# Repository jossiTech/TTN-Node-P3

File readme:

#DRAFT TTN Universal Node

(#LoRaWAN #The Things Network # TTN Universal Node  #ATmega 328p #RFM95W #1 Wire Busses #I2C #DHT11)

### Evaluation Board with nice Enclosure, providing plenty diffrent ports

# Introduction

I wanted a universal Node for The Things Network that provides diffrent ports for diffrent Purposes.
Becouse I don´t really like Breadboards I decided to design a little PCB that fits in a suitable enclosure. You can find the EAGLE-Files [here.](https://github.com/jossiTech/TTN-Node-P2/tree/master/Eagle-Files) 

* 1-Wire-Bus
* I2C
* Relais Port
* DHT11 / DHT22 Socket for temperature and humidity
* USB-B-Port for Input voltage
* Socket to connect an FTDI-Module for uploading new sketches
* SMA-Connector for Antenna

The node consist of an Arduino Pro Micro (3.3V) and a RFM95W Radio to communicate with „The Things Network.“ The RFM95W-Radio-Model use 3.3 Volt, so when using the 3.3 Volt Version of the Arduino Pro Micro no level shifting is necessary.
 
You find the suitable enclosure for the PCB by searching for "strabubox 524"
I have ordered a few PCBs from [Eurocircuits](https://www.eurocircuits.com/) and a few sets of components of my favorite chinese distributer. If you´re interested in the PCB or the PCB with the components and the enclosure you can find it on [Tindie.](https://www.tindie.com/stores/jossitech/)

[Here](https://github.com/jossiTech/TTN-Node-P2/tree/master/code) you can find the sketch that work fine for the board, feel free to use and modify it for your needs.

I descirbed HERE (add LINK) a straightforward way to visualize 4 temperatures and the humidity on Cayenne.

- The 328P comes with a Arduino Bootloader xyz
- Choose Arduino Nano 328P in the IDE when uploading new sketches

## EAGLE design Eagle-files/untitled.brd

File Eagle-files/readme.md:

### Eagle-files for The JossiTec P3 (1.1) PCB

A suitable case is available in which the PCB fits perfectly. Search for "strapubox 524"

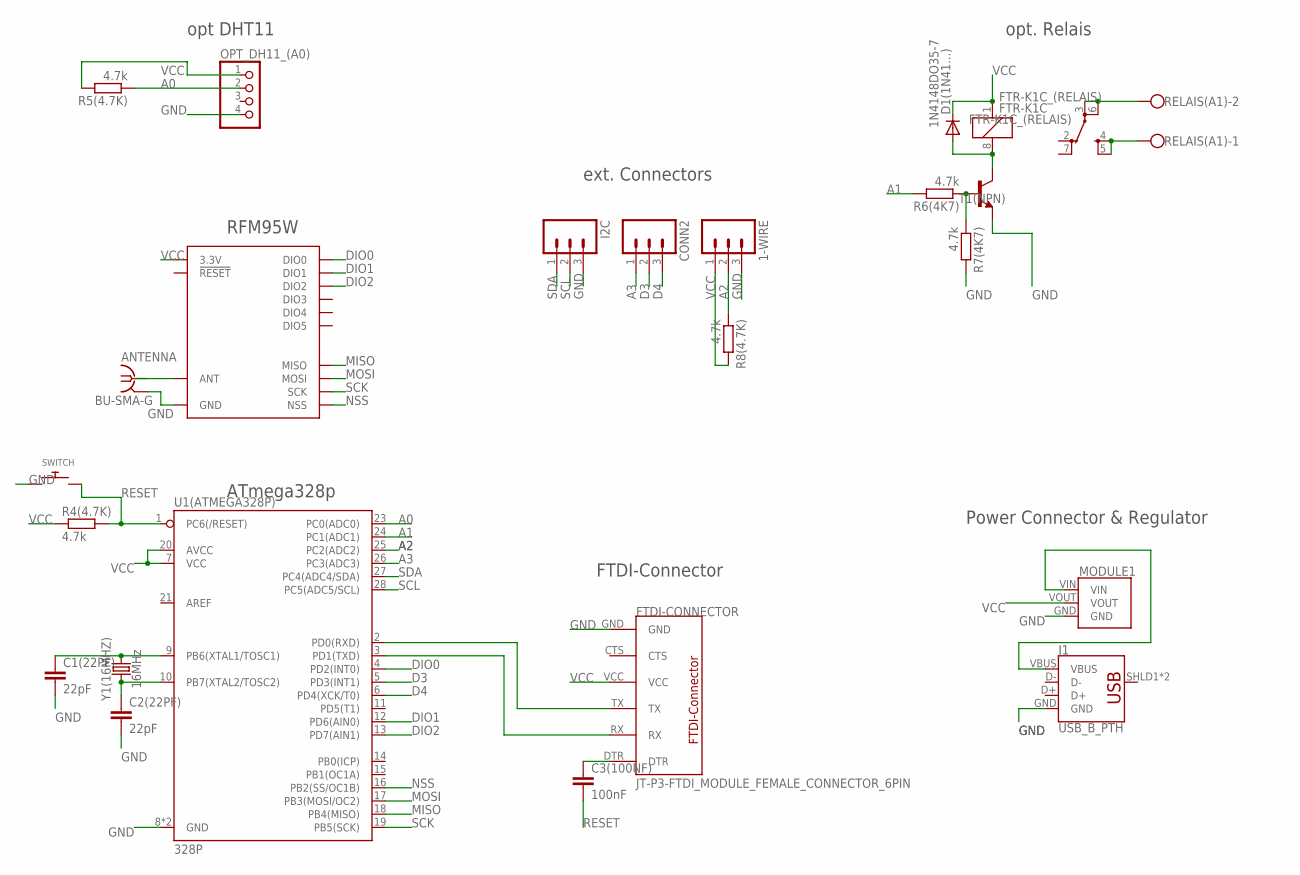
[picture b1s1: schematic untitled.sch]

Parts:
1-WIRE: M03; 03P
ANTENNA: BU-SMA-G
C1(22PF), C2(22PF): 22pF; CAP-PTH-2.54
C3(100NF): 100nF; CAP-PTH-2.54
CONN2: M03; 03P
D1(1N41...): 1N4148DO35-7; DO35-7
FTDI-CONNECTOR: JT-P3-FTDI_MODULE_FEMALE_CONNECTOR_6PIN
FTR-K1C_(RELAIS): FTR-K1C
I2C: M03; 03P
J1: USB_B_PTH; USB-B-PTH
MODULE1: JT-P3-VOLTAGEREGULATOR
OPT_DH11_(A0): PINHD-1X4; 1X04
R4(4.7K), R5(4.7K), R6(4K7), R7(4K7), R8(4.7K): 4.7k; 0207/10
RELAIS(A1): W237-102
SWITCH: SWITCH_PUSHBUTTONEVQ-PE; TACT_PANA-EVQ
T1(NPN): BC237-NPN-TO92-CBE; TO92-CBE
U1(ATMEGA328P): 328P; DIP28
U2: RFM95W; RFM95/96/97/98W
Y1(16MHZ): 16MHz; HC49US

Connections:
A0: OPT_DH11_(A0).2, R5(4.7K).1, U1(ATMEGA328P).23 (PC0(ADC0))
A1: R6(4K7).2, U1(ATMEGA328P).24 (PC1(ADC1))
A2: 1-WIRE.2, R8(4.7K).1, U1(ATMEGA328P).25 (PC2(ADC2))
A3: CONN2.1, U1(ATMEGA328P).26 (PC3(ADC3))
D3: CONN2.2, U1(ATMEGA328P).5 (PD3(INT1))
D4: CONN2.3, U1(ATMEGA328P).6 (PD4(XCK/T0))
DIO0: U1(ATMEGA328P).4 (PD2(INT0)), U2.DIO0
DIO1: U1(ATMEGA328P).12 (PD6(AIN0)), U2.DIO1
DIO2: U1(ATMEGA328P).13 (PD7(AIN1)), U2.DIO2
GND: 1-WIRE.3, ANTENNA.2, ANTENNA.3 (2), ANTENNA.4 (2), ANTENNA.5 (2), C1(22PF).2, C2(22PF).2, FTDI-CONNECTOR.GND, I2C.3, J1.GND, MODULE1.GND, OPT_DH11_(A0).4, R7(4K7).2, SWITCH.P$1, T1(NPN).E, U1(ATMEGA328P).8 (GND), U1(ATMEGA328P).22 (GND), U2.GND@1 (GND), U2.GND@2 (GND), U2.GND@3 (GND)
MISO: U1(ATMEGA328P).18 (PB4(MISO)), U2.MISO
MOSI: U1(ATMEGA328P).17 (PB3(MOSI/OC2)), U2.MOSI
unnamed: ANTENNA.1, U2.ANT
unnamed: J1.VBUS, MODULE1.VIN
unnamed: FTDI-CONNECTOR.TX, U1(ATMEGA328P).2 (PD0(RXD))
unnamed: C1(22PF).1, U1(ATMEGA328P).9 (PB6(XTAL1/TOSC1)), Y1(16MHZ).2
unnamed: FTDI-CONNECTOR.RX, U1(ATMEGA328P).3 (PD1(TXD))
unnamed: C3(100NF).1, FTDI-CONNECTOR.DTR
unnamed: C2(22PF).1, U1(ATMEGA328P).10 (PB7(XTAL2/TOSC2)), Y1(16MHZ).1
unnamed: D1(1N41...).A, FTR-K1C_(RELAIS).8 (2), T1(NPN).C
unnamed: R6(4K7).1, R7(4K7).1, T1(NPN).B
unnamed: FTR-K1C_(RELAIS).4 (SA), FTR-K1C_(RELAIS).5 (SB), RELAIS(A1).1
unnamed: FTR-K1C_(RELAIS).3 (PA), FTR-K1C_(RELAIS).6 (PB), RELAIS(A1).2
NSS: U1(ATMEGA328P).16 (PB2(SS/OC1B)), U2.NSS
RESET: C3(100NF).2, R4(4.7K).2, SWITCH.P$2, U1(ATMEGA328P).1 (PC6(/RESET))
SCK: U1(ATMEGA328P).19 (PB5(SCK)), U2.SCK
SCL: I2C.2, U1(ATMEGA328P).28 (PC5(ADC5/SCL))
SDA: I2C.1, U1(ATMEGA328P).27 (PC4(ADC4/SDA))
VCC: 1-WIRE.1, D1(1N41...).C, FTDI-CONNECTOR.VCC, FTR-K1C_(RELAIS).1, MODULE1.VOUT, OPT_DH11_(A0).1, R4(4.7K).1, R5(4.7K).2, R8(4.7K).2, U1(ATMEGA328P).7 (VCC), U1(ATMEGA328P).20 (AVCC), U2.3.3V

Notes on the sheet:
RFM95W
ATmega328p
FTDI-Connector
opt. Relais
opt DHT11
ext. Connectors
Power Connector & Regulator

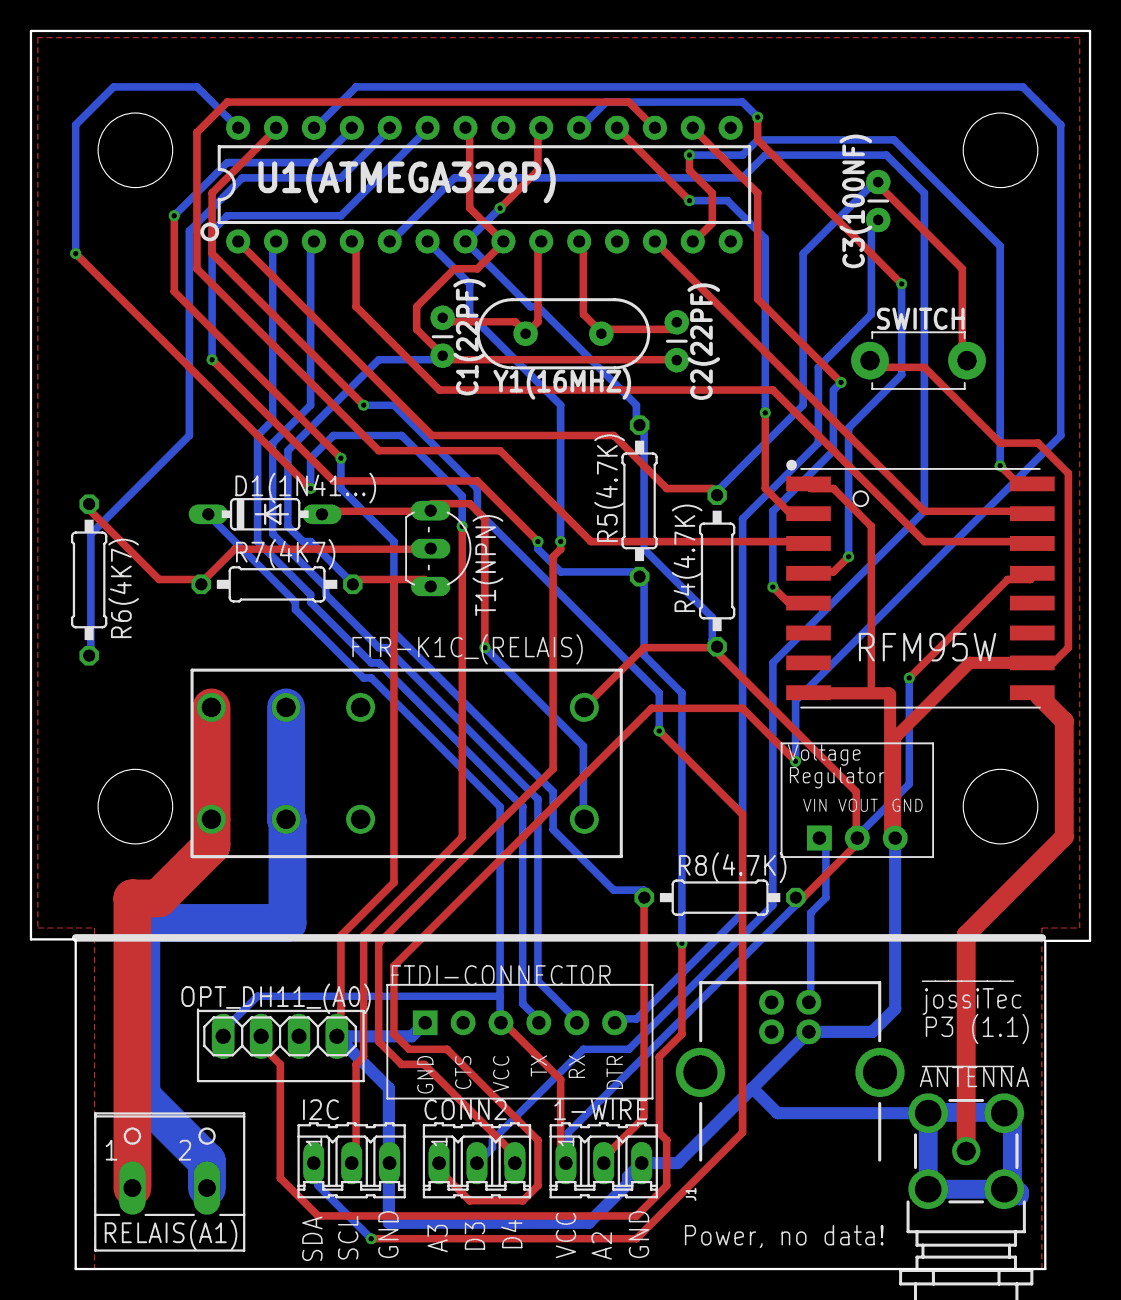
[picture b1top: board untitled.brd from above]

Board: 2 copper layers, 71.0 x 83.0 mm, 24 parts (0 on the bottom side), 29 nets.

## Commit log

2019-07-12 Rename readme to readme.md
2019-07-12 remove to large files
2019-07-12 add images
2019-07-12 Create JT-P3-1.1-Example Arduino Sketch
2019-07-12 image
2019-08-10 Update JT-P3-1.1-Example Arduino Sketch

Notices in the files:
parts and their libraries:
SparkFun-RF: Licensing: Creative Commons ShareAlike 4.0 International - https://creativecommons.org/licenses/by-sa/4.0
